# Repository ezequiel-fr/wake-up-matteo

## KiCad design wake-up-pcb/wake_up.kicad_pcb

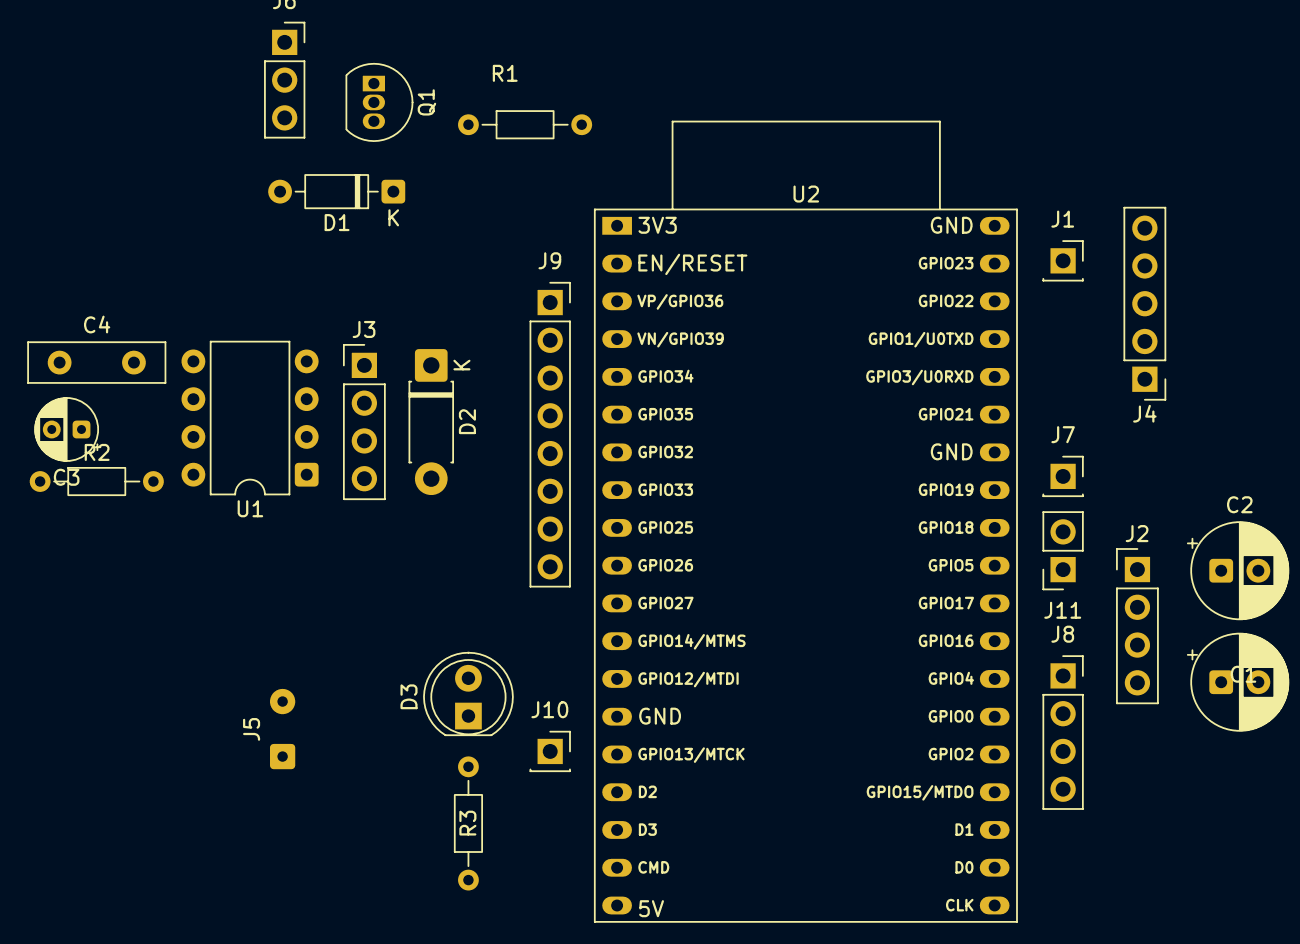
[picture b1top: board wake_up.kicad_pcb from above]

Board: 2 copper layers, 24 parts (0 on the bottom side), 36 nets, no tracks yet.

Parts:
C1, C2: 470 µF; CP_Radial_D6.3mm_P2.50mm
C3: 1 µF; CP_Radial_D4.0mm_P2.00mm
C4: 0.01 µF; C_Disc_D9.0mm_W2.5mm_P5.00mm
D1: 1N4148; D_DO-35_SOD27_P7.62mm_Horizontal
D2: 1N5819; D_DO-41_SOD81_P7.62mm_Horizontal
D3: BLUE LED; LED_D5.0mm
J1, J7, J10: Conn_01x01_Pin; PinSocket_1x01_P2.54mm_Vertical
J2: Screen; PinHeader_1x04_P2.54mm_Vertical
J3: Wireless control; PinHeader_1x04_P2.54mm_Vertical
J4: DS3231; PinHeader_1x05_P2.54mm_Vertical
J5: Conn_01x02; SolderWire-0.127sqmm_1x02_P3.7mm_D0.48mm_OD1mm
J6: Relay; PinSocket_1x03_P2.54mm_Vertical
J8: Conn_01x04; PinSocket_1x04_P2.54mm_Vertical
J9: Conn_01x08_Pin; PinSocket_1x08_P2.54mm_Vertical
J11: Conn_01x02_Pin; PinSocket_1x02_P2.54mm_Vertical
Q1: 2N3904; TO-92_Inline
R1: 1 kOhms; R_Axial_DIN0204_L3.6mm_D1.6mm_P7.62mm_Horizontal
R2: 1 MOhms; R_Axial_DIN0204_L3.6mm_D1.6mm_P7.62mm_Horizontal
R3: 47 Ohms; R_Axial_DIN0204_L3.6mm_D1.6mm_P7.62mm_Horizontal
U1: NE555P; DIP-8_W7.62mm
U2: ESP32-DevKitC

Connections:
+3.3V: J3.2, J4.1, R2.2, U1.4 (R), U1.8 (VCC), U2.1 (5v)
+5V: C1.1, C2.1, J2.1, J5.2, J6.1, U2.19 (3.3v)
GNDREF: C1.2, C2.2, C3.1, C4.1, J2.4, J3.1, J4.5, J5.1, J6.2, Q1.1 (E), R3.1, U1.1 (GND), U2.2 (GPIO11), U2.14 (GPIO35), U2.32 (GND), U2.38 (GND)
unnamed: D1.2 (A), J6.3
unnamed: D1.1 (K), Q1.3 (C)
unnamed: D2.2 (A), J3.4, U1.2 (TR)
unnamed: D2.1 (K), J3.3
unnamed: D3.2 (A), U2.13 (GPIO32)
unnamed: D3.1 (K), R3.2
unnamed: J1.1 (Pin_1_1), U2.37 (GPIO23)
unnamed: J2.2, U2.28 (GPIO17)
unnamed: J2.3, U2.27 (GPIO16)
unnamed: J4.2, U2.33 (GPIO21)
unnamed: J4.3, U2.36 (GPIO22)
unnamed: J7.1 (Pin_1_1), U2.31 (GPIO19)
unnamed: J8.1, U2.26 (GPIO4)
unnamed: J8.2, U2.25 (GPIO0)
unnamed: J8.3, U2.24 (GPIO2)
unnamed: J8.4, U2.23 (GPIO15)
unnamed: J9.1, U2.3 (GPIO10)
unnamed: J9.2, U2.4 (GPIO9)
unnamed: J9.3, U2.5 (GPIO13)
unnamed: J9.4, U2.6 (GND)
unnamed: J9.5, U2.7 (GPIO12)
unnamed: J9.6, U2.8 (GPIO14)
unnamed: J9.7, U2.9 (GPIO27)
unnamed: J9.8, U2.10 (GPIO26)
unnamed: J10.1 (Pin_1_1), U2.15 (GPIO34)
unnamed: J11.1, U2.29 (GPIO5)
unnamed: J11.2, U2.30 (GPIO18)
unnamed: Q1.2 (B), R1.1
unnamed: C4.2, U1.5 (CV)
unnamed: R2.1, U1.7 (DIS)
unnamed: U1.3 (Q), U2.12 (GPIO33)
unnamed: C3.2, U1.6 (THR)
unnamed: R1.2, U2.11 (GPIO25)

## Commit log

2026-05-14 core(init): First commit
2026-05-15 core: Initialize Express server with WebSocket support and basic routing
2026-05-15 feat(ws): Enhance WebSocket connection handling with reconnection logic and heartbeat mechanism
2026-05-16 feat: Add MongoDB configuration, implement alarm management routes, and enhance frontend with weather and alarm features
2026-05-23 feat: multiple changes
2026-05-23 feat: Add initial project structure with configuration files, README, and example code
2026-05-23 refactor: code structure for improved readability and maintainability
2026-05-24 feat(arduino): Implement interaction between the two ESP32 controllers
2026-05-24 feat: Add .gitignore for secrets.h and enhance wake-up-sketch.ino with WiFi, RTC, and SD functionalities
2026-05-24 feat: Add initial UI implementation and upload script for WakeUpScreen project
2026-05-25 feat: Add weather functionality to WakeUpScreen
    - Introduced a new WeatherState structure to manage weather data including temperature, wind speed, sunrise time, and weather icon.
    - Implemented parsing for SET_WEATHER command to update weather information.
    - Created a new UI module (ui.c, ui.h) to handle user interface updates for clock and weather display.
    - Added weather icons handling with a new weather_icon module (weather_icon.c, weather_icon.h) to retrieve appropriate icons based on weather conditions.
    - Updated main application logic to synchronize UI with clock and weather data.
    - Enhanced UI styling for weather display, including day/night mode adjustments.
2026-05-25 feat: Update platformio.ini dependencies and refactor weather icon handling in UI
2026-05-25 feat: Implement weather fetching functionality in wake-up-sketch.ino
2026-05-25 feat: Enhance weather functionality with new API integration and caching
2026-05-25 feat: Improve WiFi connection handling with LED indicators and automatic reconnection
2026-05-30 feat: Add WiFi command handling and EEPROM storage for SSID and password
2026-05-30 Add initial schematic for wake-up PCB design
    - Created a new PDF file containing the schematic diagram for the wake-up PCB.
    - The schematic includes components such as the DS3231, ESP32, relays, and various resistors and capacitors.
    - This document serves as a reference for the hardware design and layout.
2026-05-30 feat: Add audio playback functionality and update upload script
2026-05-30 Refactor code structure for improved readability and maintainability
2026-05-31 refactor(schematic): updated component layout, improved connections, and enhanced readability. Upgraded to KiCad E.D.A. 10.0.3.
2026-05-31 feat: Add initial PCB and screen design files for wake-up project
2026-05-31 feat(ui): Implement sleep mode management with inactivity timer and backlight control
2026-05-31 fix(ui): Reduce inactivity timeout from 2 minutes to 30 seconds for sleep mode
2026-05-31 feat(challenges): Add mental challenge themes and activities for cognitive stimulation
